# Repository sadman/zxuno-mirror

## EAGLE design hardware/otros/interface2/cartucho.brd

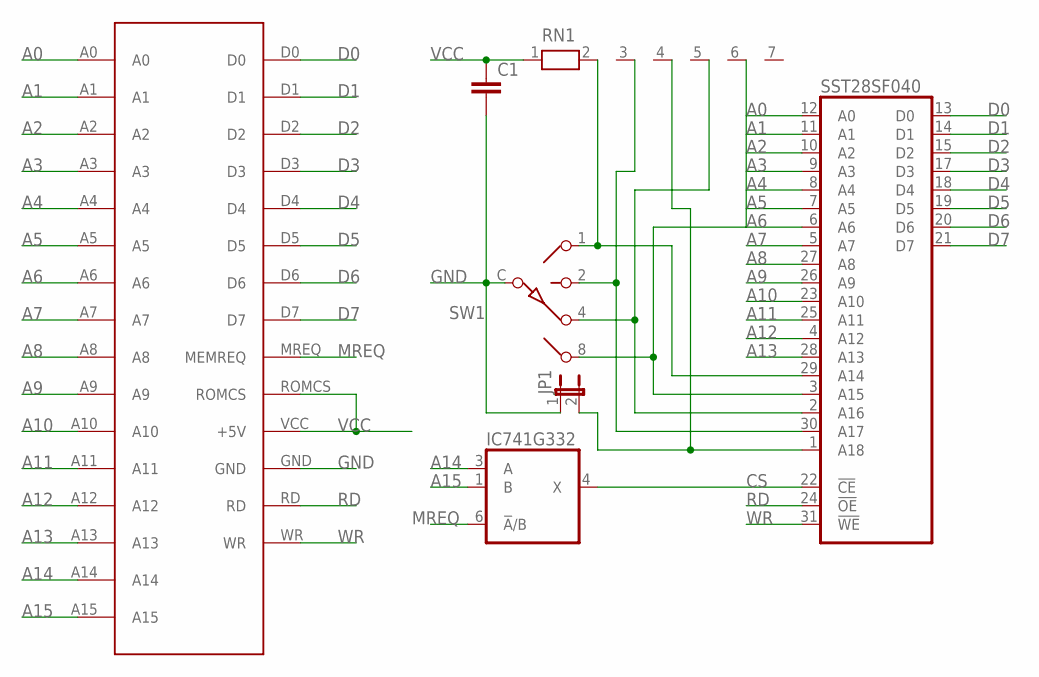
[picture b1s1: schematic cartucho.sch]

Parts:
C1: C-EUC0603; C0603
IC741G332: 741G3157DBVR; DBV_R-PDSO-G6
JP1: JP1E; JP1
RN1: RN06; RN-7
SST28SF040: SST39VF040N; PLCC32R
SW1: SW-C16
U$1: IF2BUS; BUS_CARTUCHO_IF2

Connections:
A0: SST28SF040.12 (A0), U$1.A0
A1: SST28SF040.11 (A1), U$1.A1
A2: SST28SF040.10 (A2), U$1.A2
A3: SST28SF040.9 (A3), U$1.A3
A4: SST28SF040.8 (A4), U$1.A4
A5: SST28SF040.7 (A5), U$1.A5
A6: SST28SF040.6 (A6), U$1.A6
A7: SST28SF040.5 (A7), U$1.A7
A8: SST28SF040.27 (A8), U$1.A8
A9: SST28SF040.26 (A9), U$1.A9
A10: SST28SF040.23 (A10), U$1.A10
A11: SST28SF040.25 (A11), U$1.A11
A12: SST28SF040.4 (A12), U$1.A12
A13: SST28SF040.28 (A13), U$1.A13
A14: IC741G332.3 (A), U$1.A14
A15: IC741G332.1 (B), U$1.A15
CS: IC741G332.4 (X), SST28SF040.22 (!CE)
D0: SST28SF040.13 (D0), U$1.D0
D1: SST28SF040.14 (D1), U$1.D1
D2: SST28SF040.15 (D2), U$1.D2
D3: SST28SF040.17 (D3), U$1.D3
D4: SST28SF040.18 (D4), U$1.D4
D5: SST28SF040.19 (D5), U$1.D5
D6: SST28SF040.20 (D6), U$1.D6
D7: SST28SF040.21 (D7), U$1.D7
GND: C1.2, IC741G332.2 (GND), JP1.1, SST28SF040.16 (GND), SW1.C, U$1.GND
MREQ: IC741G332.6 (!A!/B), U$1.MREQ (MEMREQ)
unnamed: JP1.2, RN1.4, SST28SF040.1 (A18)
unnamed: RN1.3, SST28SF040.30 (A17), SW1.2
unnamed: RN1.5, SST28SF040.2 (A16), SW1.4
unnamed: RN1.6, SST28SF040.3 (A15), SW1.8
unnamed: RN1.2, SST28SF040.29 (A14), SW1.1
RD: SST28SF040.24 (!OE), U$1.RD
VCC: C1.1, IC741G332.5 (VCC), RN1.1, SST28SF040.32 (VCC), U$1.ROMCS, U$1.VCC (+5V)
WR: SST28SF040.31 (!WE), U$1.WR

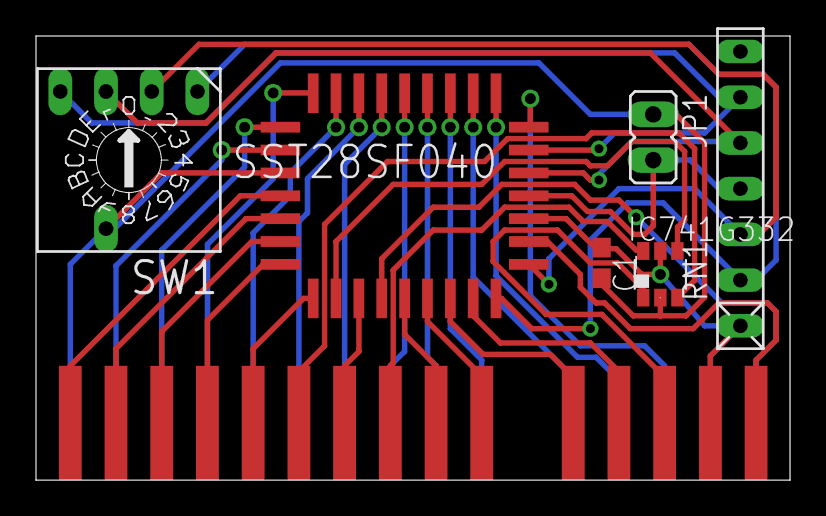
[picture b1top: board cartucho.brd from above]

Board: 2 copper layers, 41.9 x 24.7 mm, 7 parts (0 on the bottom side), 35 nets.

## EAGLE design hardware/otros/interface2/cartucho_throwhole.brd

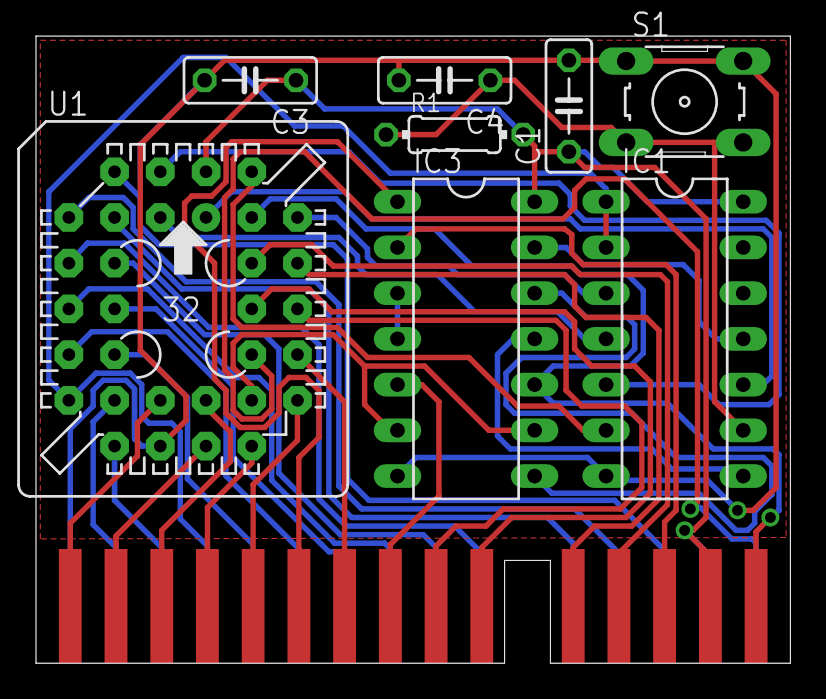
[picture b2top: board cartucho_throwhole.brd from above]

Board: 2 copper layers, 41.9 x 34.8 mm, 9 parts (0 on the bottom side), 40 nets.

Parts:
C1, C3: 100nF; C050-025X075
C4: 4.7uF; C050-025X075
IC1: 74HC164N; DIL14
IC3: 74HC32N; DIL14
R1: 10K; 0204/7
S1: RESET; B3F-10XX
U1: AM29F040S; PLCC-SR32
U$1: IF2BUS; BUS_CARTUCHO_IF2

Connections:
A0: U1.12, U$1.A0
A1: U1.11, U$1.A1
A2: U1.10, U$1.A2
A3: U1.9, U$1.A3
A4: U1.8, U$1.A4
A5: U1.7, U$1.A5
A6: U1.6, U$1.A6
A7: U1.5, U$1.A7
A8: U1.27, U$1.A8
A9: U1.26, U$1.A9
A10: U1.23, U$1.A10
A11: U1.25, U$1.A11
A12: U1.4, U$1.A12
A13: U1.28, U$1.A13
A14: IC3.1, U$1.A14
A15: IC3.2, U$1.A15
CS: IC3.6, IC3.9, U1.22
D0: IC1.1, IC1.2, U1.13, U$1.D0
D1: U1.14, U$1.D1
D2: U1.15, U$1.D2
D3: U1.17, U$1.D3
D4: U1.18, U$1.D4
D5: U1.19, U$1.D5
D6: U1.20, U$1.D6
D7: U1.21, U$1.D7
GND: C1.2, C3.2, C4.2, IC1.7, IC3.7, S1.1, S1.2, U1.16, U$1.GND
LOCK: IC1.11, IC3.13
MREQ: IC3.5, U$1.MREQ
unnamed: IC1.10, U1.1
unnamed: IC1.6, U1.30
unnamed: IC1.5, U1.2
unnamed: IC1.4, U1.3
unnamed: IC1.3, U1.29
unnamed: IC3.3, IC3.4
unnamed: IC1.8, IC3.11
unnamed: IC3.8, IC3.12
RD: U1.24, U$1.RD
RESET: C4.1, IC1.9, R1.1, S1.3, S1.4
VCC: C1.1, C3.1, IC1.14, IC3.14, R1.2, U1.32, U$1.ROMCS, U$1.VCC
WR: IC3.10, U1.31, U$1.WR

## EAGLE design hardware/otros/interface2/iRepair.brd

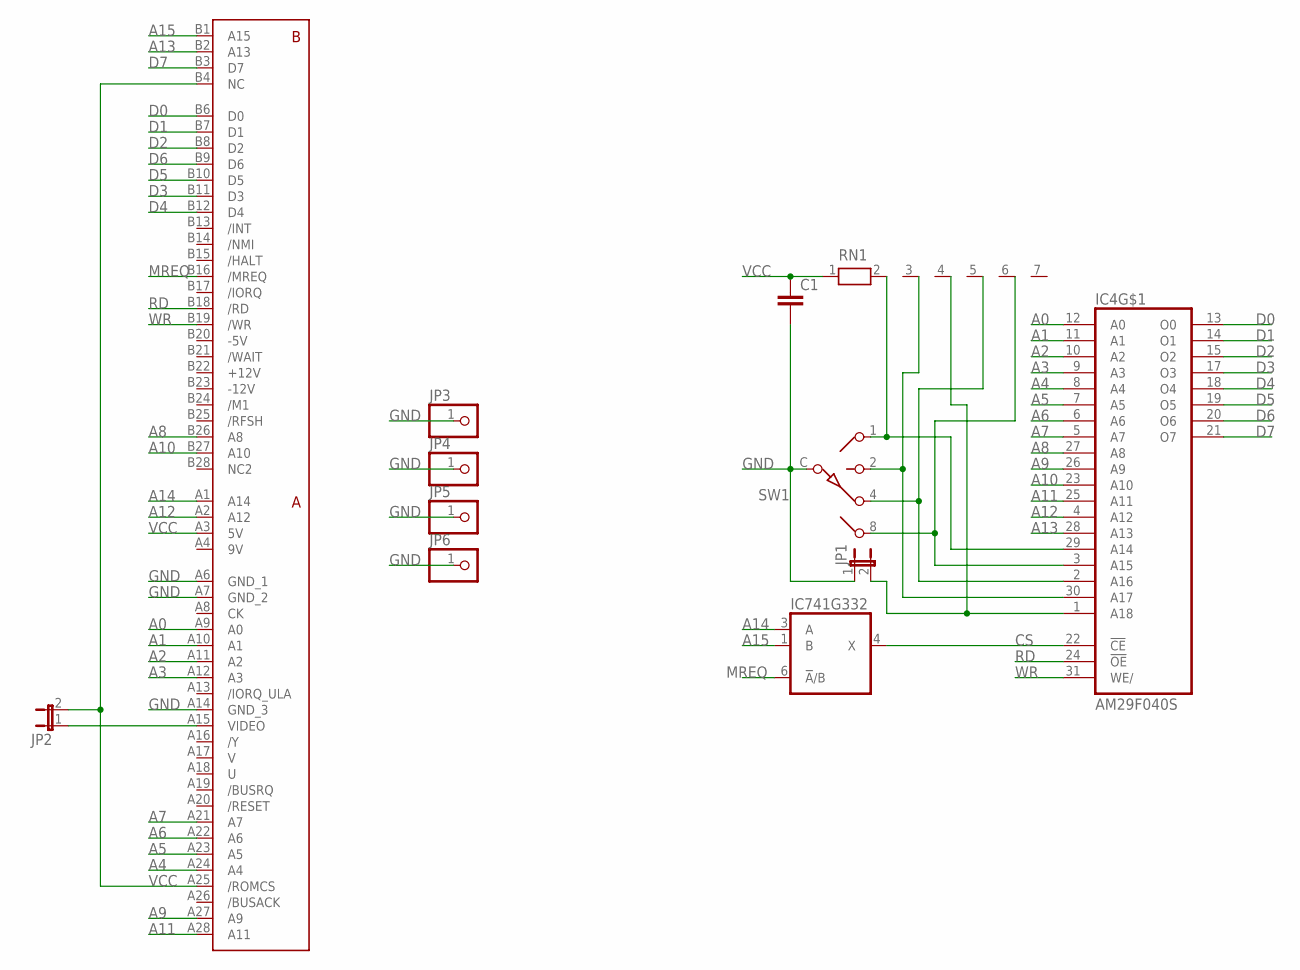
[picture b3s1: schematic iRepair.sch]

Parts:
C1: C-EU025-025X050; C025-025X050
IC4: AM29F040S; PLCC-SR32
IC741G332: 741G3157DBVR; DBV_R-PDSO-G6
JP1, JP2: JP1E; JP1
JP3, JP4, JP5, JP6: PINHD-1X1; 1X01
RN1: RN06; RN-7
SW1: SW-C16
U$3: ZXSP_ED2X28_SPE; 2X28_SPE

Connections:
9V: U$3.A4 (9V)
+12V: U$3.B22 (+12V)
-5V: U$3.B20 (-5V)
-12V: U$3.B23 (-12V)
A0: IC4.12 (A0), U$3.A9 (A0)
A1: IC4.11 (A1), U$3.A10 (A1)
A2: IC4.10 (A2), U$3.A11 (A2)
A3: IC4.9 (A3), U$3.A12 (A3)
A4: IC4.8 (A4), U$3.A24 (A4)
A5: IC4.7 (A5), U$3.A23 (A5)
A6: IC4.6 (A6), U$3.A22 (A6)
A7: IC4.5 (A7), U$3.A21 (A7)
A8: IC4.27 (A8), U$3.B26 (A8)
A9: IC4.26 (A9), U$3.A27 (A9)
A10: IC4.23 (A10), U$3.B27 (A10)
A11: IC4.25 (A11), U$3.A28 (A11)
A12: IC4.4 (A12), U$3.A2 (A12)
A13: IC4.28 (A13), U$3.B2 (A13)
A14: IC741G332.3 (A), U$3.A1 (A14)
A15: IC741G332.1 (B), U$3.B1 (A15)
CS: IC4.22 (!CE), IC741G332.4 (X)
D0: IC4.13 (O0), U$3.B6 (D0)
D1: IC4.14 (O1), U$3.B7 (D1)
D2: IC4.15 (O2), U$3.B8 (D2)
D3: IC4.17 (O3), U$3.B11 (D3)
D4: IC4.18 (O4), U$3.B12 (D4)
D5: IC4.19 (O5), U$3.B10 (D5)
D6: IC4.20 (O6), U$3.B9 (D6)
D7: IC4.21 (O7), U$3.B3 (D7)
GND: C1.2, IC4.16 (GND), IC741G332.2 (GND), JP1.1, JP3.1, JP4.1, JP5.1, JP6.1, SW1.C, U$3.A6 (GND_1), U$3.A7 (GND_2), U$3.A14 (GND_3)
MREQ: IC741G332.6 (!A!/B), U$3.B16 (/MREQ)
unnamed: JP2.1, U$3.A15 (VIDEO)
unnamed: IC4.1 (A18), JP1.2, RN1.4
unnamed: IC4.30 (A17), RN1.3, SW1.2
unnamed: IC4.2 (A16), RN1.5, SW1.4
unnamed: IC4.3 (A15), RN1.6, SW1.8
unnamed: IC4.29 (A14), RN1.2, SW1.1
RD: IC4.24 (!OE), U$3.B18 (/RD)
VCC: C1.1, IC4.32 (VCC), IC741G332.5 (VCC), JP2.2, RN1.1, U$3.A3 (5V), U$3.A25 (/ROMCS), U$3.B4 (NC)
WR: IC4.31 (WE/), U$3.B19 (/WR)

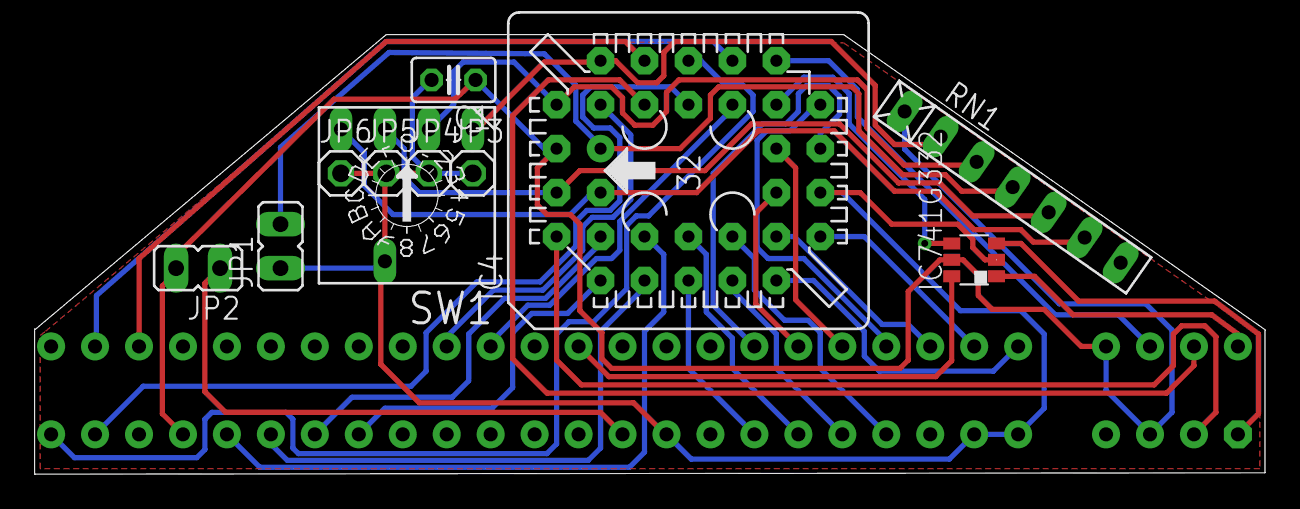
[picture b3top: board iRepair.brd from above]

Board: 2 copper layers, 71.1 x 25.4 mm, 12 parts (1 on the bottom side), 36 nets.

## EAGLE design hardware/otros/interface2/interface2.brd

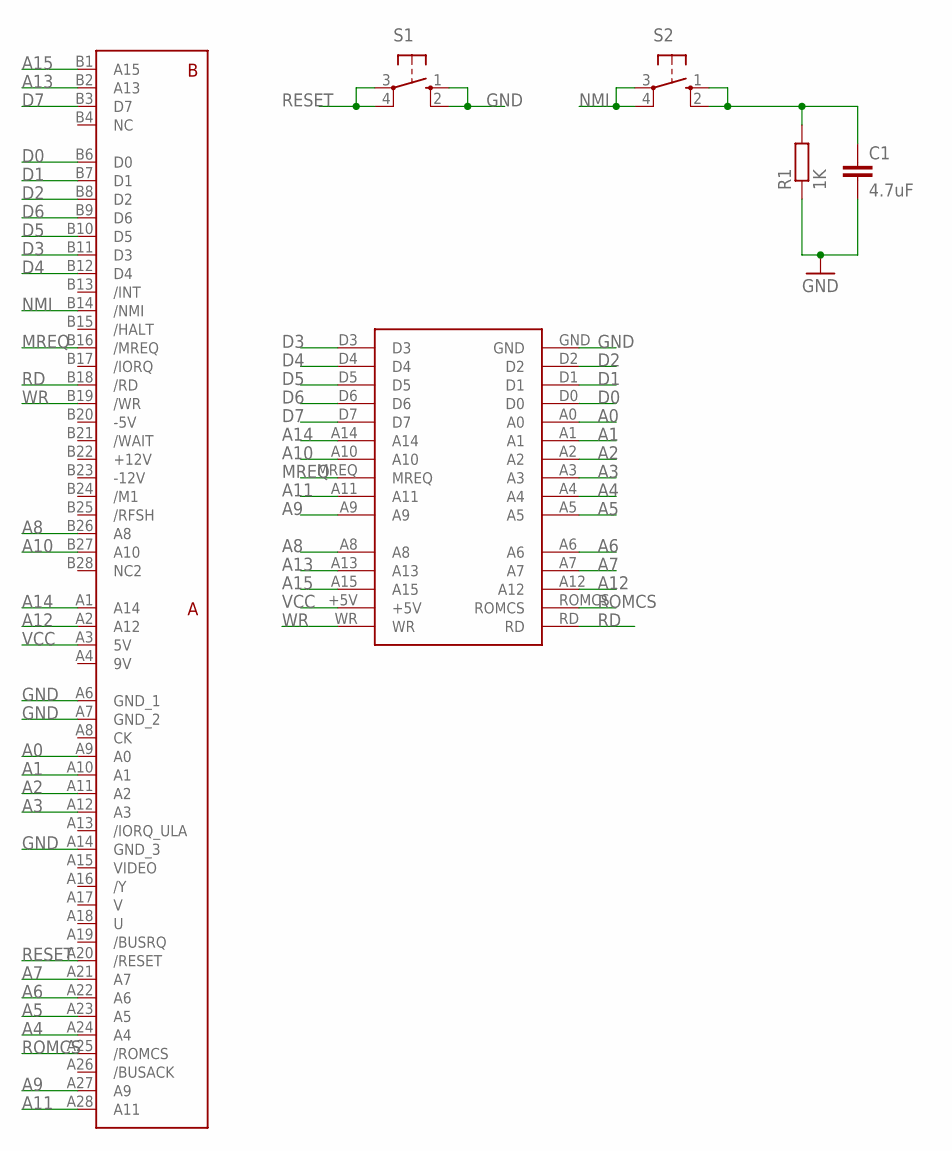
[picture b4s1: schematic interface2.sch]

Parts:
C1: 4.7uF; C025-025X050
R1: 1K; 0204/5
S1, S2: 10-XX; B3F-10XX
U$1: ZX_CARTRIDGE
U$3: ZXSP_ED2X28_SPE; 2X28_SPE

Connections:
9V: U$3.A4 (9V)
+12V: U$3.B22 (+12V)
-5V: U$3.B20 (-5V)
-12V: U$3.B23 (-12V)
A0: U$1.A0, U$3.A9 (A0)
A1: U$1.A1, U$3.A10 (A1)
A2: U$1.A2, U$3.A11 (A2)
A3: U$1.A3, U$3.A12 (A3)
A4: U$1.A4, U$3.A24 (A4)
A5: U$1.A5, U$3.A23 (A5)
A6: U$1.A6, U$3.A22 (A6)
A7: U$1.A7, U$3.A21 (A7)
A8: U$1.A8, U$3.B26 (A8)
A9: U$1.A9, U$3.A27 (A9)
A10: U$1.A10, U$3.B27 (A10)
A11: U$1.A11, U$3.A28 (A11)
A12: U$1.A12, U$3.A2 (A12)
A13: U$1.A13, U$3.B2 (A13)
A14: U$1.A14, U$3.A1 (A14)
A15: U$1.A15, U$3.B1 (A15)
D0: U$1.D0, U$3.B6 (D0)
D1: U$1.D1, U$3.B7 (D1)
D2: U$1.D2, U$3.B8 (D2)
D3: U$1.D3, U$3.B11 (D3)
D4: U$1.D4, U$3.B12 (D4)
D5: U$1.D5, U$3.B10 (D5)
D6: U$1.D6, U$3.B9 (D6)
D7: U$1.D7, U$3.B3 (D7)
GND: C1.2, R1.1, S1.1 (S), S1.2 (S1), U$1.GND, U$3.A6 (GND_1), U$3.A7 (GND_2), U$3.A14 (GND_3)
MREQ: U$1.MREQ, U$3.B16 (/MREQ)
unnamed: C1.1, R1.2, S2.1 (S), S2.2 (S1)
NMI: S2.3, S2.4 (P1), U$3.B14 (/NMI)
RD: U$1.RD, U$3.B18 (/RD)
RESET: S1.3, S1.4 (P1), U$3.A20 (/RESET)
ROMCS: U$1.ROMCS, U$3.A25 (/ROMCS)
VCC: U$1.+5V, U$3.A3 (5V)
WR: U$1.WR, U$3.B19 (/WR)

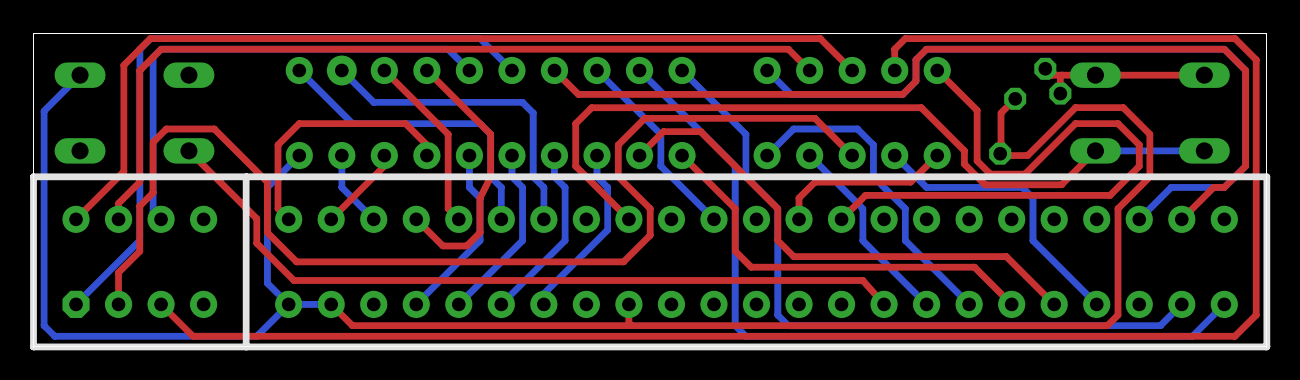
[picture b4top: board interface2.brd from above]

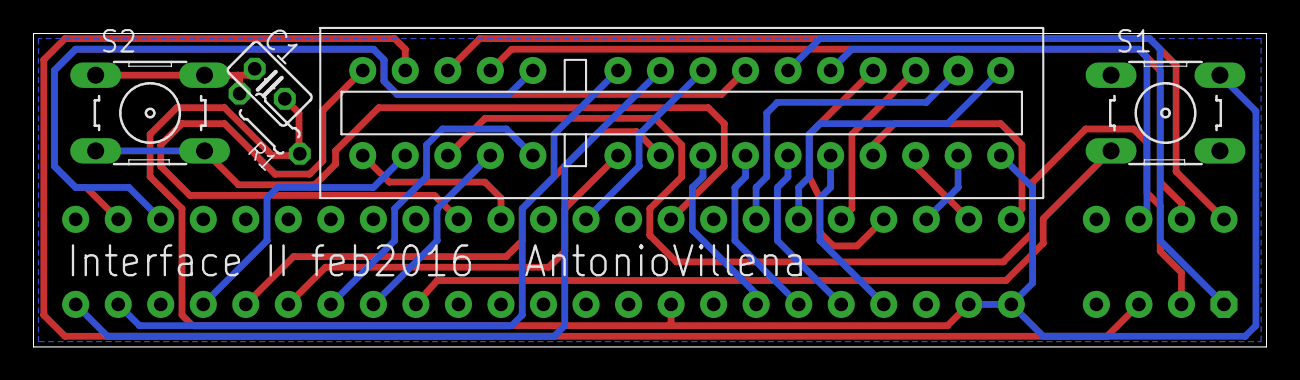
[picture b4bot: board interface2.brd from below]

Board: 2 copper layers, 73.6 x 18.7 mm, 6 parts (5 on the bottom side), 33 nets.

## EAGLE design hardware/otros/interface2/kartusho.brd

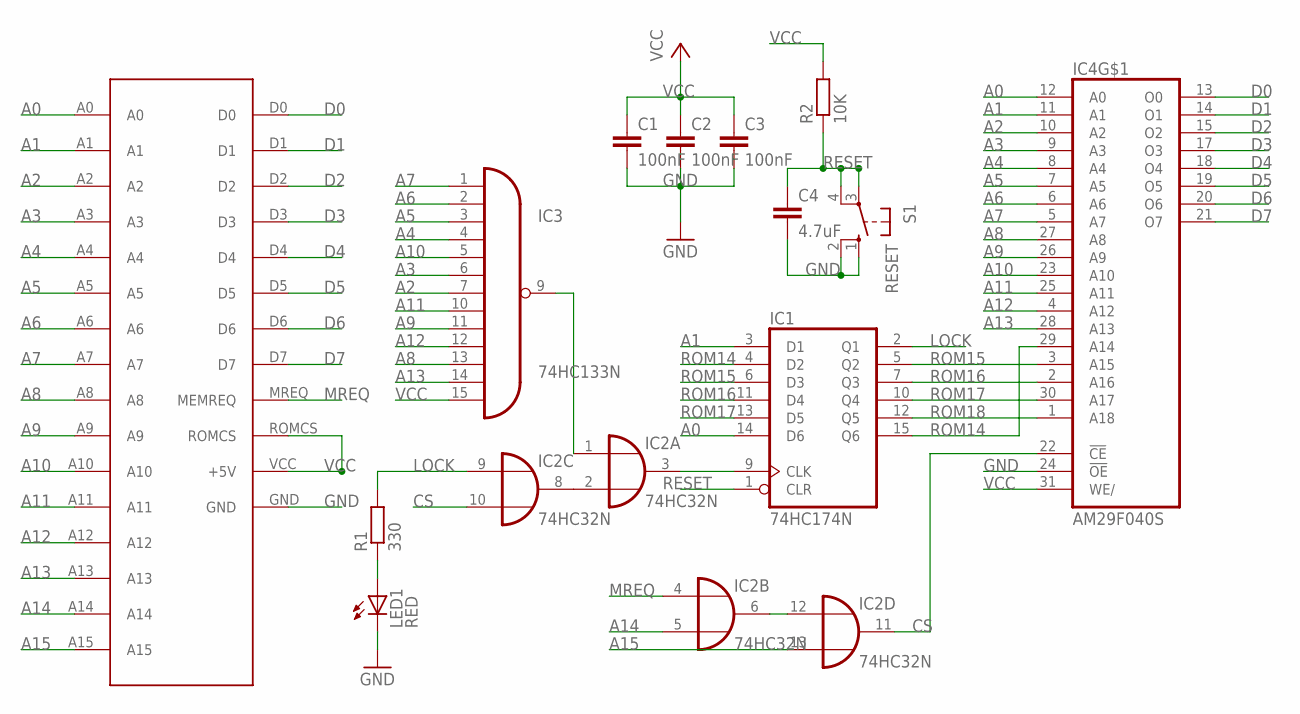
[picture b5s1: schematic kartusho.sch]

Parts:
C1, C3: 100nF; C050-025X075
C2: 100nF; C025-025X050
C4: 4.7uF; C025-025X050
IC1: 74HC174N; DIL16
IC2: 74HC32N; DIL14
IC3: 74HC133N; DIL16
IC4: AM29F040S; PLCC-SR32
LED1: RED; LED3MM
R1: 330; 0204/7
R2: 10K; 0204/7
S1: RESET; B3F-10XX
U$1: IF2BUS; BUS_CARTUCHO_IF2

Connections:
A0: IC1.14 (D6), IC4.12 (A0), U$1.A0
A1: IC1.3 (D1), IC4.11 (A1), U$1.A1
A2: IC3.7 (I6), IC4.10 (A2), U$1.A2
A3: IC3.6 (I5), IC4.9 (A3), U$1.A3
A4: IC3.4 (I3), IC4.8 (A4), U$1.A4
A5: IC3.3 (I2), IC4.7 (A5), U$1.A5
A6: IC3.2 (I1), IC4.6 (A6), U$1.A6
A7: IC3.1 (I0), IC4.5 (A7), U$1.A7
A8: IC3.13 (I10), IC4.27 (A8), U$1.A8
A9: IC3.11 (I8), IC4.26 (A9), U$1.A9
A10: IC3.5 (I4), IC4.23 (A10), U$1.A10
A11: IC3.10 (I7), IC4.25 (A11), U$1.A11
A12: IC3.12 (I9), IC4.4 (A12), U$1.A12
A13: IC3.14 (I11), IC4.28 (A13), U$1.A13
A14: IC2.5 (I1), U$1.A14
A15: IC2.13 (I1), U$1.A15
CS: IC2.10 (I1), IC2.11 (O), IC4.22 (!CE)
D0: IC4.13 (O0), U$1.D0
D1: IC4.14 (O1), U$1.D1
D2: IC4.15 (O2), U$1.D2
D3: IC4.17 (O3), U$1.D3
D4: IC4.18 (O4), U$1.D4
D5: IC4.19 (O5), U$1.D5
D6: IC4.20 (O6), U$1.D6
D7: IC4.21 (O7), U$1.D7
GND: C1.2, C2.2, C3.2, C4.2, IC1.8 (GND), IC2.7 (GND), IC3.8 (GND), IC4.16 (GND), IC4.24 (!OE), LED1.K (C), S1.1 (S), S1.2 (S1), U$1.GND
LOCK: IC1.2 (Q1), IC2.9 (I0), R1.2
MREQ: IC2.4 (I0), U$1.MREQ (MEMREQ)
unnamed: IC1.9 (CLK), IC2.3 (O)
unnamed: IC2.6 (O), IC2.12 (I0)
unnamed: IC2.2 (I1), IC2.8 (O)
unnamed: IC2.1 (I0), IC3.9 (O)
unnamed: LED1.A, R1.1
RESET: C4.1, IC1.1 (CLR), R2.1, S1.3, S1.4 (P1)
ROM14: IC1.4 (D2), IC1.15 (Q6), IC4.29 (A14)
ROM15: IC1.5 (Q2), IC1.6 (D3), IC4.3 (A15)
ROM16: IC1.7 (Q3), IC1.11 (D4), IC4.2 (A16)
ROM17: IC1.10 (Q4), IC1.13 (D5), IC4.30 (A17)
ROM18: IC1.12 (Q5), IC4.1 (A18)
VCC: C1.1, C2.1, C3.1, IC1.16 (VCC), IC2.14 (VCC), IC3.15 (I12), IC3.16 (VCC), IC4.31 (WE/), IC4.32 (VCC), R2.2, U$1.ROMCS, U$1.VCC (+5V)

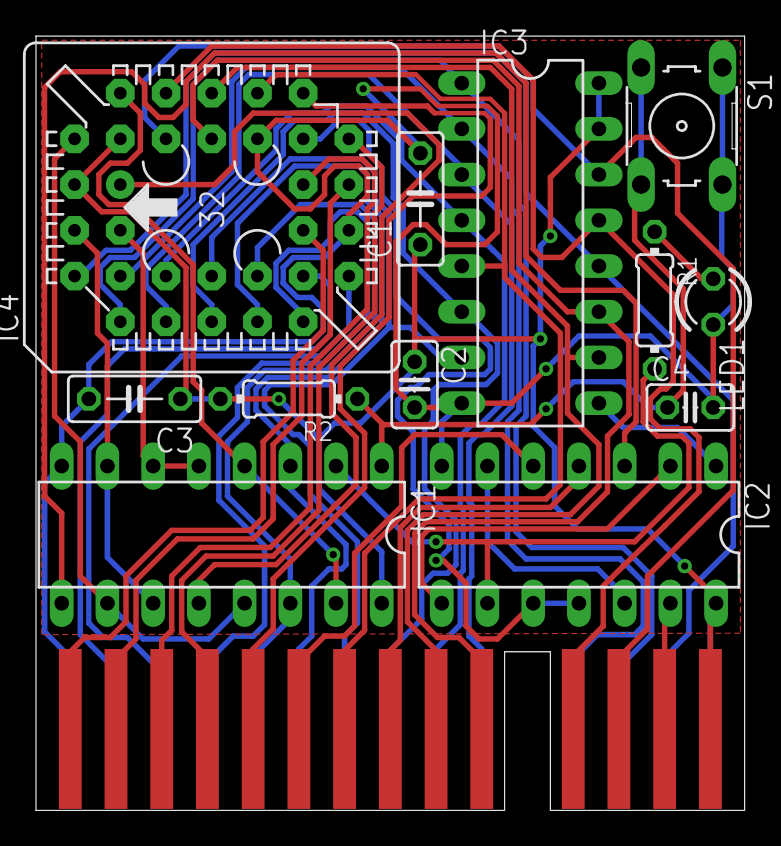
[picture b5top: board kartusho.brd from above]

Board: 2 copper layers, 39.4 x 43.0 mm, 13 parts (0 on the bottom side), 40 nets.

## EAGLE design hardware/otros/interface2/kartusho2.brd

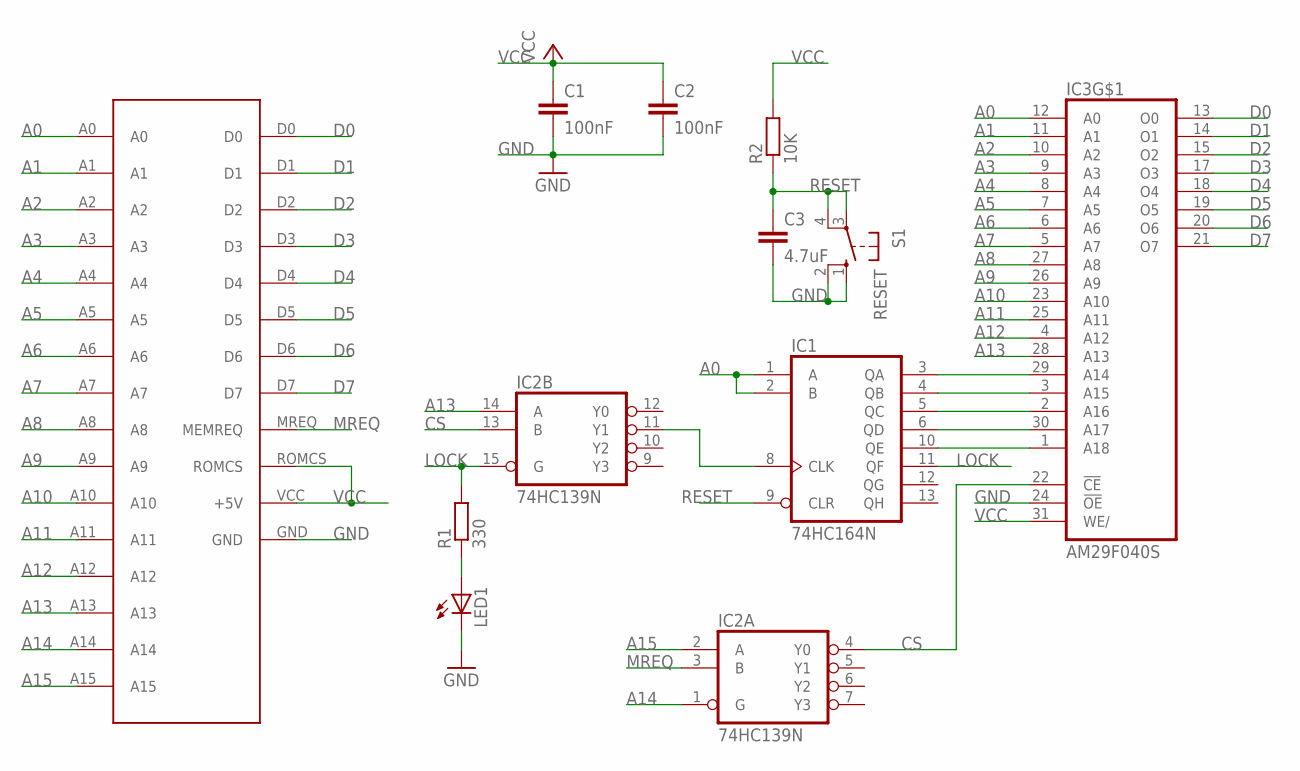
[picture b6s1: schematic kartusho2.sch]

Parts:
C1, C2: 100nF; C025-025X050
C3: 4.7uF; C025-025X050
IC1: 74HC164N; DIL14
IC2: 74HC139N; DIL16
IC3: AM29F040S; PLCC-SR32
LED1: LED3MM
R1: 330; 0204/7
R2: 10K; 0204/7
S1: RESET; B3F-10XX
U$1: IF2BUS; BUS_CARTUCHO_IF2

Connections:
A0: IC1.1 (A), IC1.2 (B), IC3.12 (A0), U$1.A0
A1: IC3.11 (A1), U$1.A1
A2: IC3.10 (A2), U$1.A2
A3: IC3.9 (A3), U$1.A3
A4: IC3.8 (A4), U$1.A4
A5: IC3.7 (A5), U$1.A5
A6: IC3.6 (A6), U$1.A6
A7: IC3.5 (A7), U$1.A7
A8: IC3.27 (A8), U$1.A8
A9: IC3.26 (A9), U$1.A9
A10: IC3.23 (A10), U$1.A10
A11: IC3.25 (A11), U$1.A11
A12: IC3.4 (A12), U$1.A12
A13: IC2.14 (A), IC3.28 (A13), U$1.A13
A14: IC2.1 (G), U$1.A14
A15: IC2.2 (A), U$1.A15
CS: IC2.4 (Y0), IC2.13 (B), IC3.22 (!CE)
D0: IC3.13 (O0), U$1.D0
D1: IC3.14 (O1), U$1.D1
D2: IC3.15 (O2), U$1.D2
D3: IC3.17 (O3), U$1.D3
D4: IC3.18 (O4), U$1.D4
D5: IC3.19 (O5), U$1.D5
D6: IC3.20 (O6), U$1.D6
D7: IC3.21 (O7), U$1.D7
GND: C1.2, C2.2, C3.2, IC1.7 (GND), IC2.8 (GND), IC3.16 (GND), IC3.24 (!OE), LED1.K (C), S1.1 (S), S1.2 (S1), U$1.GND
LOCK: IC1.11 (QF), IC2.15 (G), R1.2
MREQ: IC2.3 (B), U$1.MREQ (MEMREQ)
unnamed: IC1.8 (CLK), IC2.11 (Y1)
unnamed: IC1.10 (QE), IC3.1 (A18)
unnamed: IC1.6 (QD), IC3.30 (A17)
unnamed: IC1.5 (QC), IC3.2 (A16)
unnamed: IC1.4 (QB), IC3.3 (A15)
unnamed: IC1.3 (QA), IC3.29 (A14)
unnamed: LED1.A, R1.1
RESET: C3.1, IC1.9 (CLR), R2.1, S1.3, S1.4 (P1)
VCC: C1.1, C2.1, IC1.14 (VCC), IC2.16 (VCC), IC3.31 (WE/), IC3.32 (VCC), R2.2, U$1.ROMCS, U$1.VCC (+5V)

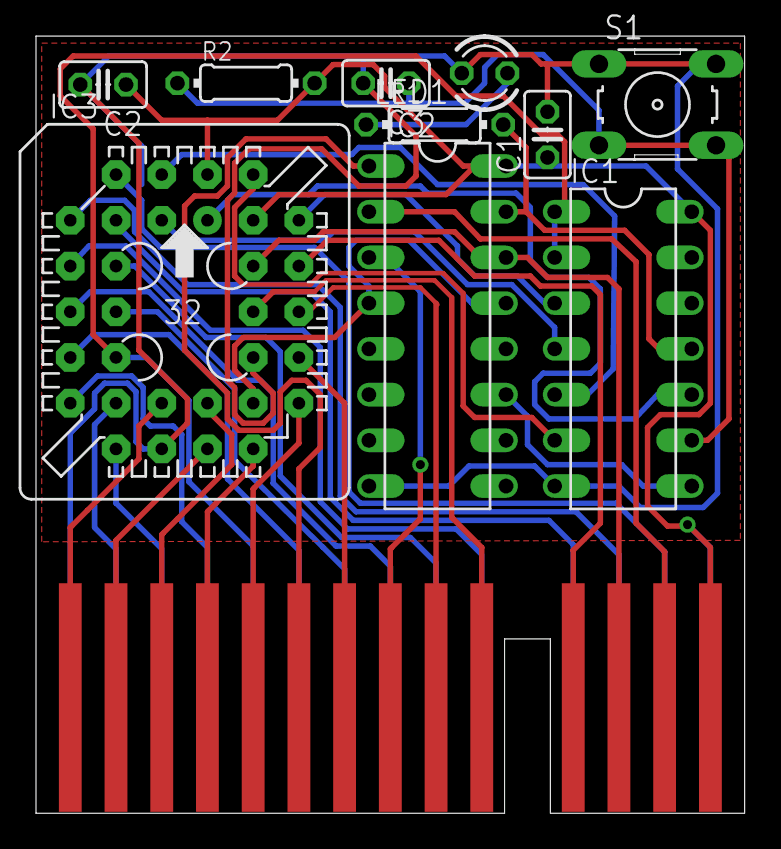
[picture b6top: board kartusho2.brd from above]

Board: 2 copper layers, 39.4 x 43.2 mm, 11 parts (0 on the bottom side), 37 nets.
